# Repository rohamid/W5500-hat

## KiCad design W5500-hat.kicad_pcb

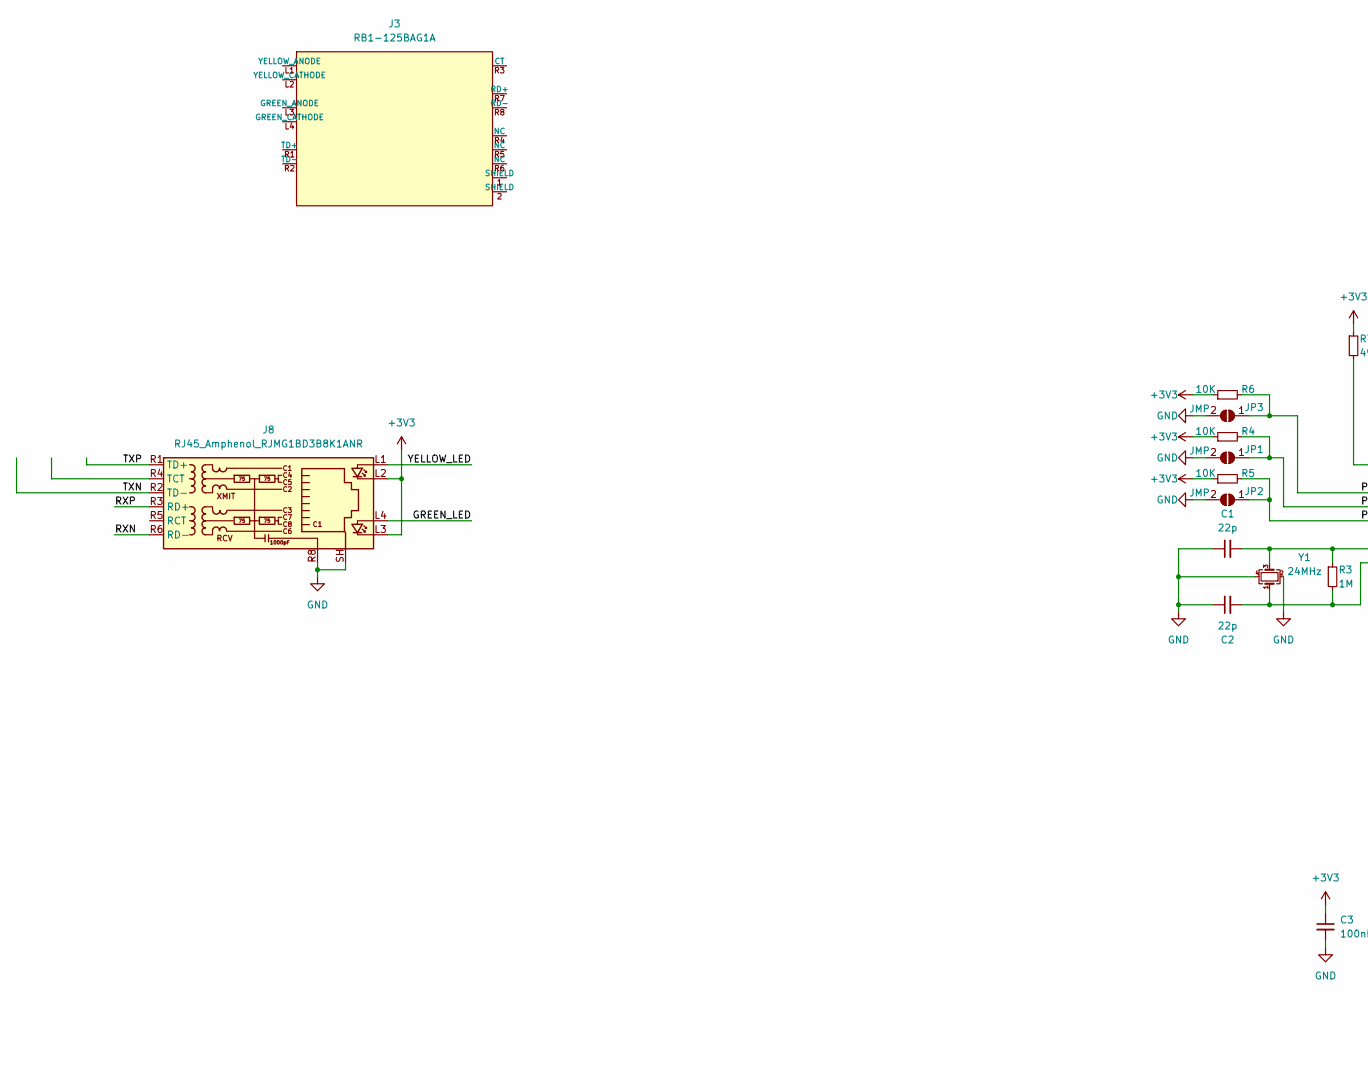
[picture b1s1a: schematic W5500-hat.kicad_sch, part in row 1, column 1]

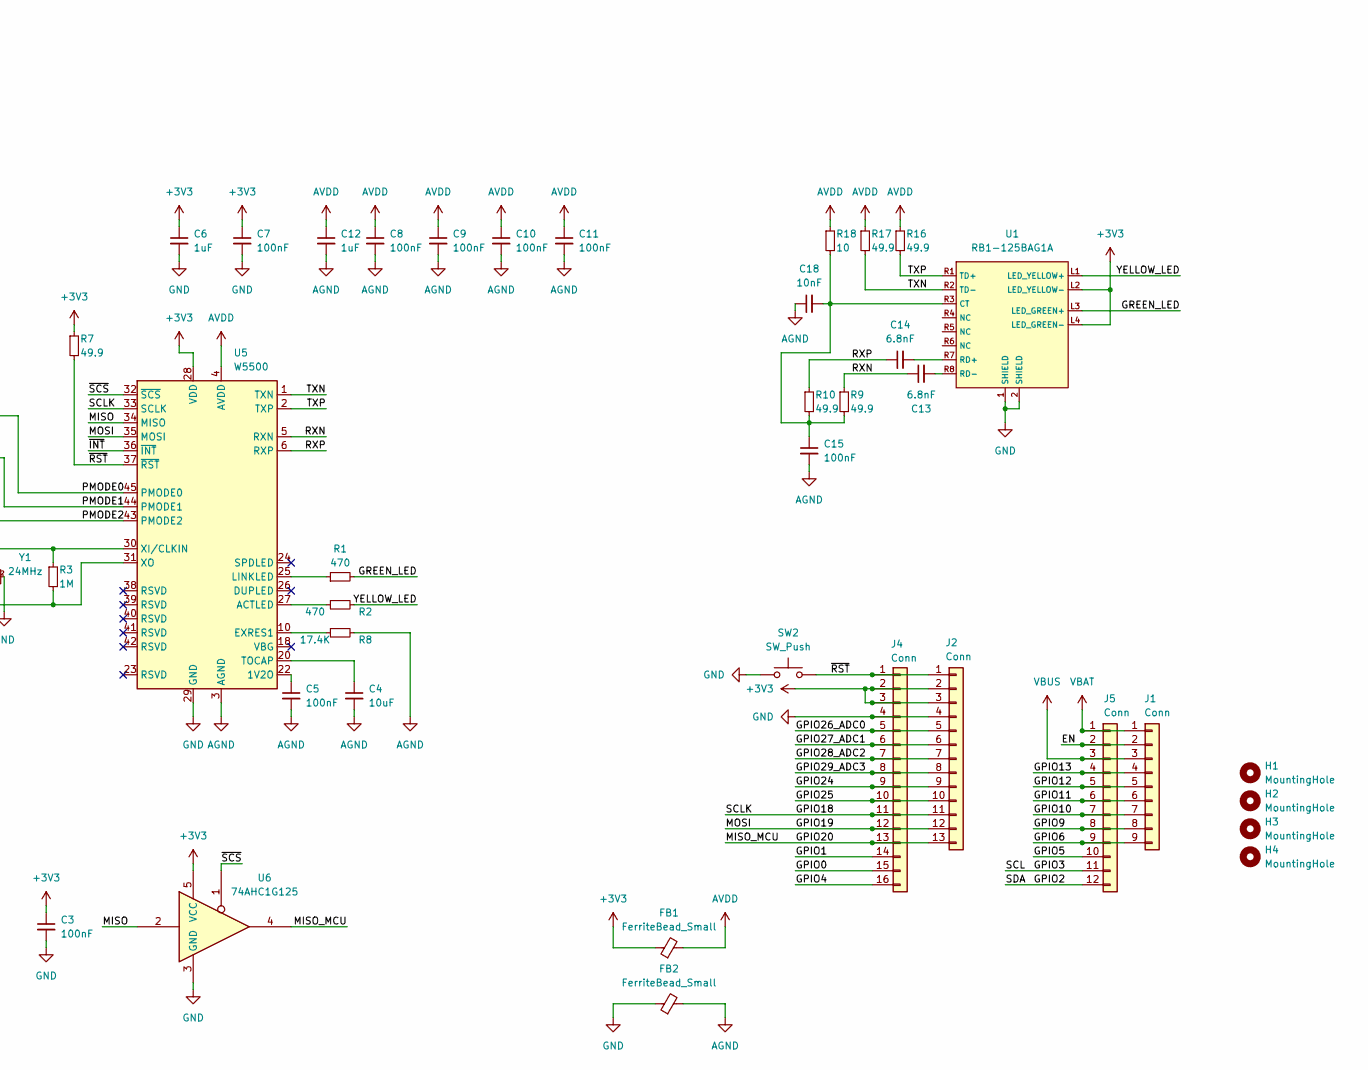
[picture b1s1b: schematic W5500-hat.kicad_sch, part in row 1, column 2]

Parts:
C1, C2: 22p; C_0402_1005Metric
C3, C5, C7, C8, C9, C10, C11, C15: 100nF; C_0402_1005Metric
C4: 10uF; C_0603_1608Metric
C6, C12: 1uF; C_0603_1608Metric
C13, C14: 6.8nF; C_0402_1005Metric
C18: 10nF; C_0402_1005Metric
FB1, FB2: FerriteBead_Small; L_0603_1608Metric
H1, H2, H3, H4: MountingHole; MountingHole_2.5mm
J1: Conn; PinHeader_1x09_P2.54mm_Vertical
J2: Conn; PinHeader_1x13_P2.54mm_Vertical
J3: RB1-125BAG1A; WIZnet-RB1-125BAG1A-0; mouser part number 950-RB1-125BAG1A; digikey description CONN MAGJACK 1PORT 100 BASE-T
J4: Conn; PinHeader_1x16_P2.54mm_Vertical
J5: Conn; PinHeader_1x12_P2.54mm_Vertical
J8: RJ45_Amphenol_RJMG1BD3B8K1ANR
JP1, JP2, JP3: JMP; SolderJumper-2_P1.3mm_Open_RoundedPad1.0x1.5mm
R1, R2: 470; R_0402_1005Metric
R3: 1M; R_0402_1005Metric
R4, R5, R6: 10K; R_0402_1005Metric
R7, R9, R10, R16, R17: 49.9; R_0402_1005Metric
R8: 17.4K; R_0402_1005Metric
R18: 10; R_0402_1005Metric
SW2: SW_Push; SW_SPST_PTS810
U1: RB1-125BAG1A; WIZnet-RB1-125BAG1A-0
U5: W5500; LQFP-48_7x7mm_P0.5mm
U6: 74AHC1G125; SOT-23-5
Y1: 24MHz; Crystal_SMD_2520-4Pin_2.5x2.0mm

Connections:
+3V3: C3.1, C6.1, C7.1, FB1.1, J2.2, J2.3, J4.2, J4.3, J8.L2, J8.L3, R4.1, R5.1, R6.1, R7.1, U1.L2 (LED_YELLOW-), U1.L4 (LED_GREEN-), U5.28 (VDD), U6.5 (VCC)
/EN: J1.2, J5.2
/GPIO0: J4.15
/GPIO1: J4.14
/GPIO2: J5.12
/GPIO3: J5.11
/GPIO4: J4.16
/GPIO5: J5.10
/GPIO6: J1.9, J5.9
/GPIO9: J1.8, J5.8
/GPIO10: J1.7, J5.7
/GPIO11: J1.6, J5.6
/GPIO12: J1.5, J5.5
/GPIO13: J1.4, J5.4
/GPIO18: J2.11, J4.11, U5.33 (SCLK)
/GPIO19: J2.12, J4.12, U5.35 (MOSI)
/GPIO20: J2.13, J4.13, U6.4
/GPIO24: J2.9, J4.9
/GPIO25: J2.10, J4.10
/GPIO26_ADC0: J2.5, J4.5
/GPIO27_ADC1: J2.6, J4.6
/GPIO28_ADC2: J2.7, J4.7
/GPIO29_ADC3: J2.8, J4.8
/GREEN_LED: J8.L4, R1.2, U1.L3 (LED_GREEN+)
/MISO: U5.34 (MISO), U6.2
/PMODE0: JP3.1 (A), R6.2, U5.45 (PMODE0)
/PMODE1: JP1.1 (A), R4.2, U5.44 (PMODE1)
/PMODE2: JP2.1 (A), R5.2, U5.43 (PMODE2)
/RXN: C13.1, J8.R6 (RD-), R9.1, U5.5 (RXN)
/RXP: C14.1, J8.R3 (RD+), R10.1, U5.6 (RXP)
/TXN: J8.R2 (TD-), R17.2, U1.R2 (TD-), U5.1 (TXN)
/TXP: J8.R1 (TD+), R16.2, U1.R1 (TD+), U5.2 (TXP)
/YELLOW_LED: J8.L1, R2.2, U1.L1 (LED_YELLOW+)
/~INT: U5.36 (~INT)
/~RST: J2.1, J4.1, R7.2, SW2.2, U5.37 (~RST)
/~SCS: U5.32 (~SCS), U6.1
AGND: C4.2, C5.2, C8.2, C9.2, C10.2, C11.2, C12.2, C15.2, C18.1, FB2.2, R8.2, U5.3 (AGND), U5.9 (AGND), U5.14 (AGND), U5.16 (AGND), U5.19 (AGND), U5.48 (AGND)
AVDD: C8.1, C9.1, C10.1, C11.1, C12.1, FB1.2, R16.1, R17.1, R18.1, U5.4 (AVDD), U5.8 (AVDD), U5.11 (AVDD), U5.15 (AVDD), U5.17 (AVDD), U5.21 (AVDD)
GND: C1.1, C2.1, C3.2, C6.2, C7.2, FB2.1, J2.4, J4.4, J8.R8, J8.SH, JP1.2 (B), JP2.2 (B), JP3.2 (B), SW2.1, U1.1 (SHIELD), U1.2 (SHIELD), U5.29 (GND), U6.3 (GND), Y1.2, Y1.4
unnamed: C15.1, C18.2, R9.2, R10.2, R18.2, U1.R3 (CT)
unnamed: C14.2, U1.R7 (RD+)
unnamed: C13.2, U1.R8 (RD-)
unnamed: C5.1, U5.22 (1V2O)
unnamed: R2.1, U5.27 (ACTLED)
unnamed: R8.1, U5.10 (EXRES1)
unnamed: R1.1, U5.25 (LINKLED)
unnamed: C4.1, U5.20 (TOCAP)
unnamed: C1.2, R3.1, U5.30 (XI/CLKIN), Y1.3
unnamed: C2.2, R3.2, U5.31 (XO), Y1.1
VBAT: J1.1, J5.1
VBUS: J1.3, J5.3

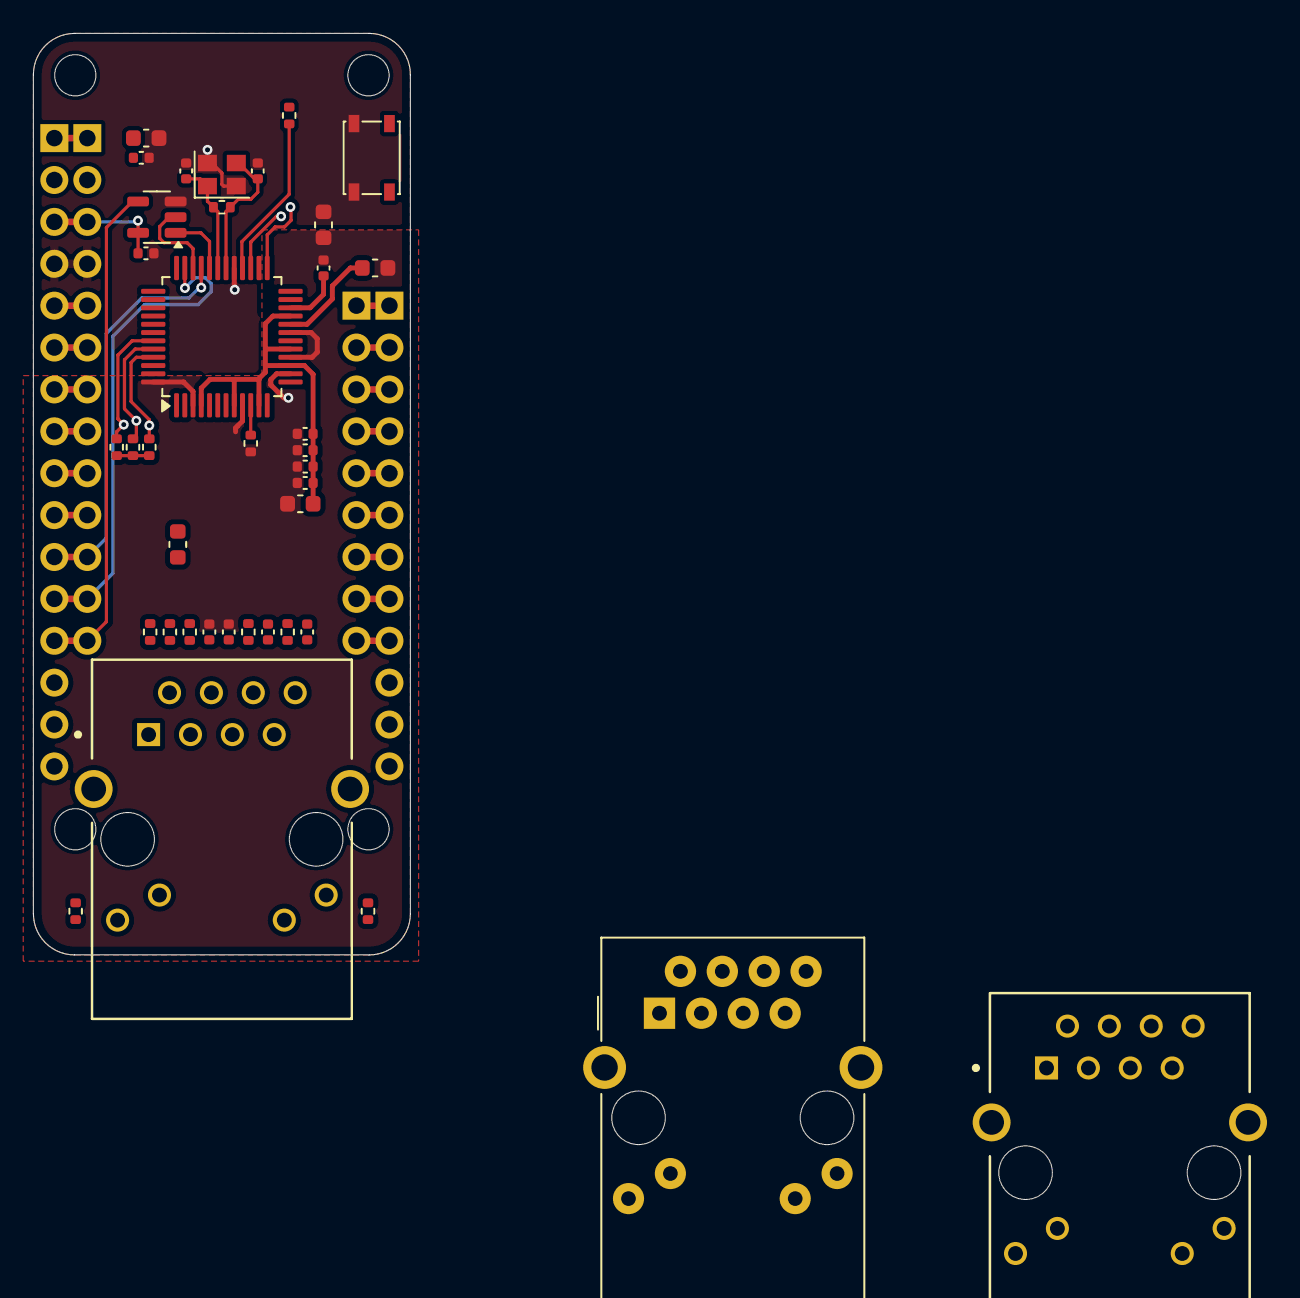
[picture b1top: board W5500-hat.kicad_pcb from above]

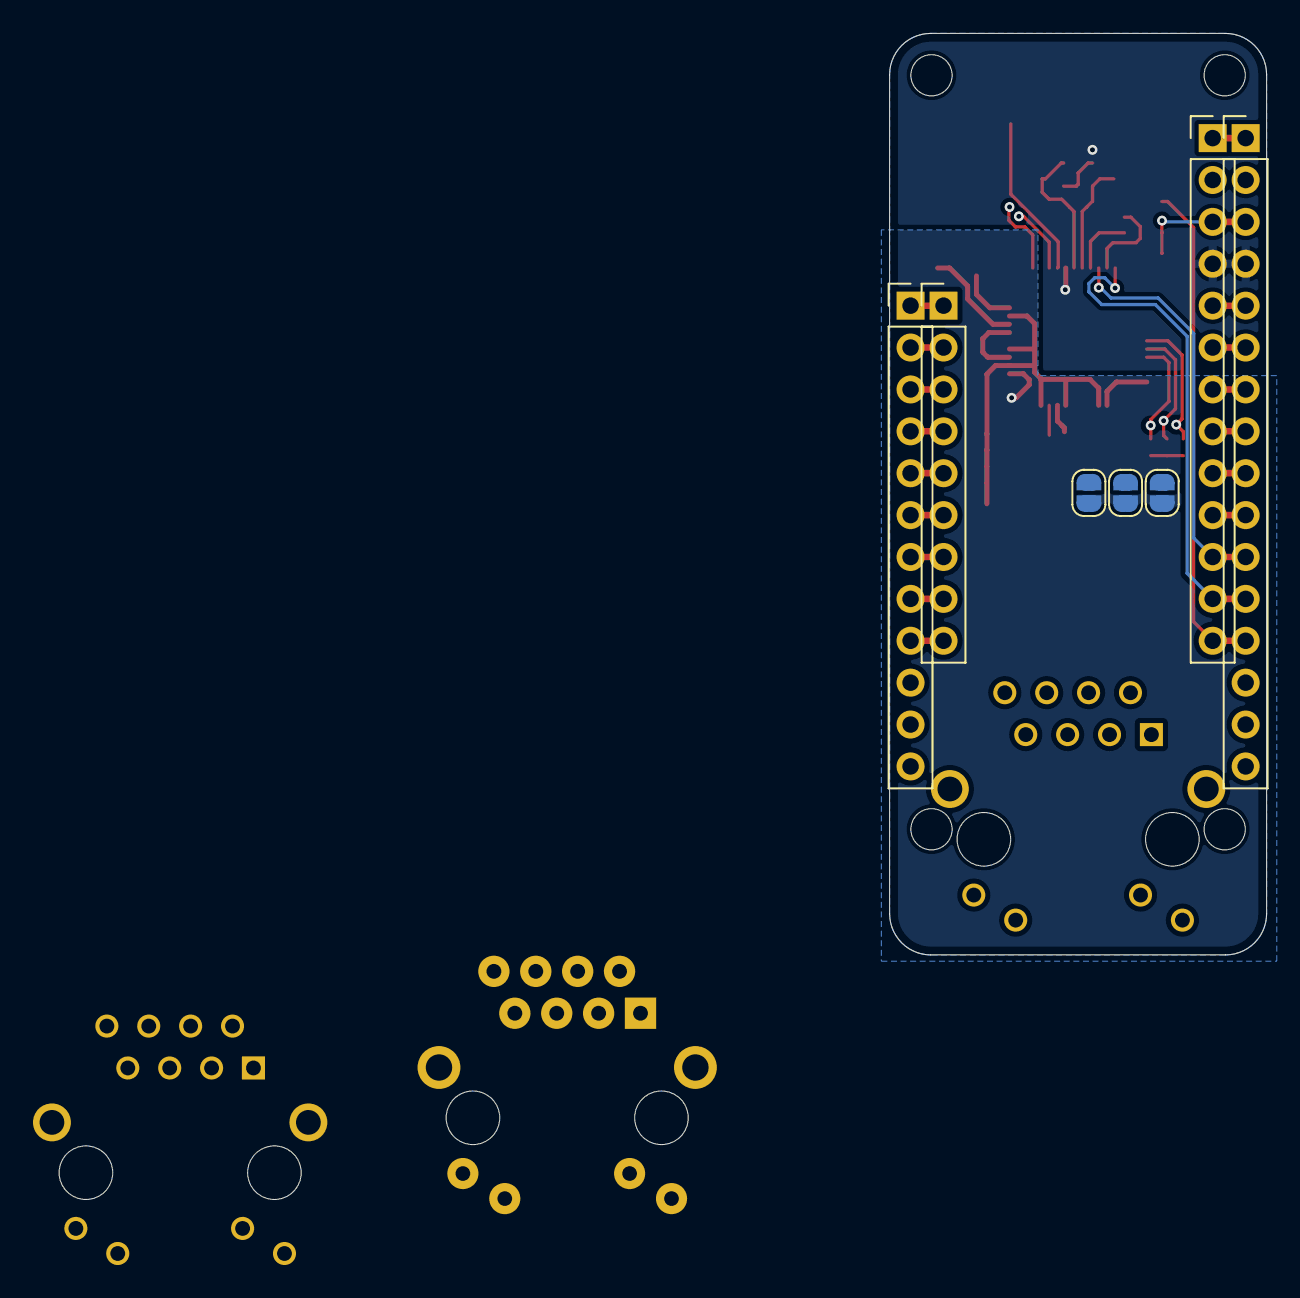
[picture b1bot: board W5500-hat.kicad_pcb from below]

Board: 2 copper layers, 22.9 x 55.9 mm, 49 parts (7 on the bottom side), 44 nets.

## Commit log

2024-03-19 Tracks almost finished
2024-03-20 Need RJ45 alternative for W5500 not W5500s
